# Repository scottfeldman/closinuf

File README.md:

# closinuf

**3D point scanner** — live 3D coordinates from four quadrature encoders on a Raspberry Pi, with a small web UI, foot‑switch capture, and FreeCAD‑friendly export.

## What it does

- Tracks **X**, **X'**, **Y**, **Z** from dedicated rotary encoders.  
- **Capture Point** in the browser or a **GPIO foot switch** appends the current **(X, Y, Z)** to a list (mm internally).
- **Save** downloads an **ASC** point cloud file, which can be imported into FreeCAD as a point cloud. 
- **Units** cycles mm → m → in → ft. **Zero** clears counts and points.
- **Short beep** on capture when audio output is available (speakers or HDMI).

## Hardware

See [HARDWARE.md](HARDWARE.md).

## Install on the Pi (`install.sh`)

1. On the Pi, clone the repository and enter the project directory:

   ```bash
   git clone https://github.com/scottfeldman/closinuf.git
   cd closinuf
   ```

2. Run the install script as root:

   ```bash
   sudo ./install.sh
   ```

3. Reboot if the installer prompts you to. 

What the script does:

- Enables **SPI** and relocates kernel CE pins off GPIO 8/7 (`dtoverlay=spi0-2cs,cs0_pin=12,cs1_pin=13`) in `/boot/firmware/config.txt`.
- Installs **`alsa-utils`** (`aplay` for capture beep) and **`golang-go`** if `go` is missing.
- Builds **`./closinuf`** in the repo.
- Adds the install user to **`spi`** and **`gpio`** groups (for local `go build` / debugging without the service).
- Installs **closinuf** **systemd** services: **`closinuf.service`** (app on :3000, runs as **root** for `/dev/mem` GPCLK, SPI, and GPIO), **`closinuf-browser.service`** (Chromium as install user)
- Prompts to **reboot** when SPI settings were added to `config.txt` (first install)

Useful commands:

```bash
sudo systemctl status closinuf closinuf-browser
sudo journalctl -u closinuf -f
```

## Manual run (development)

```bash
go build -o closinuf .
sudo ./closinuf
```

Open `http://127.0.0.1:3000`. Root is required for GPCLK setup (`/dev/mem`); the systemd service runs as root for the same reason.

## ASC export

One point per line: `X Y Z` in **millimeters** (space‑separated), suitable for FreeCAD point cloud import.

## Stack

Fiber, HTMX, gomponents, **LS7366R** counters over **SPI0**, **go-gpiocdev** (chip selects + foot switch).

## License

MIT — see [LICENSE](LICENSE).

## Author

Scott Feldman (2026)

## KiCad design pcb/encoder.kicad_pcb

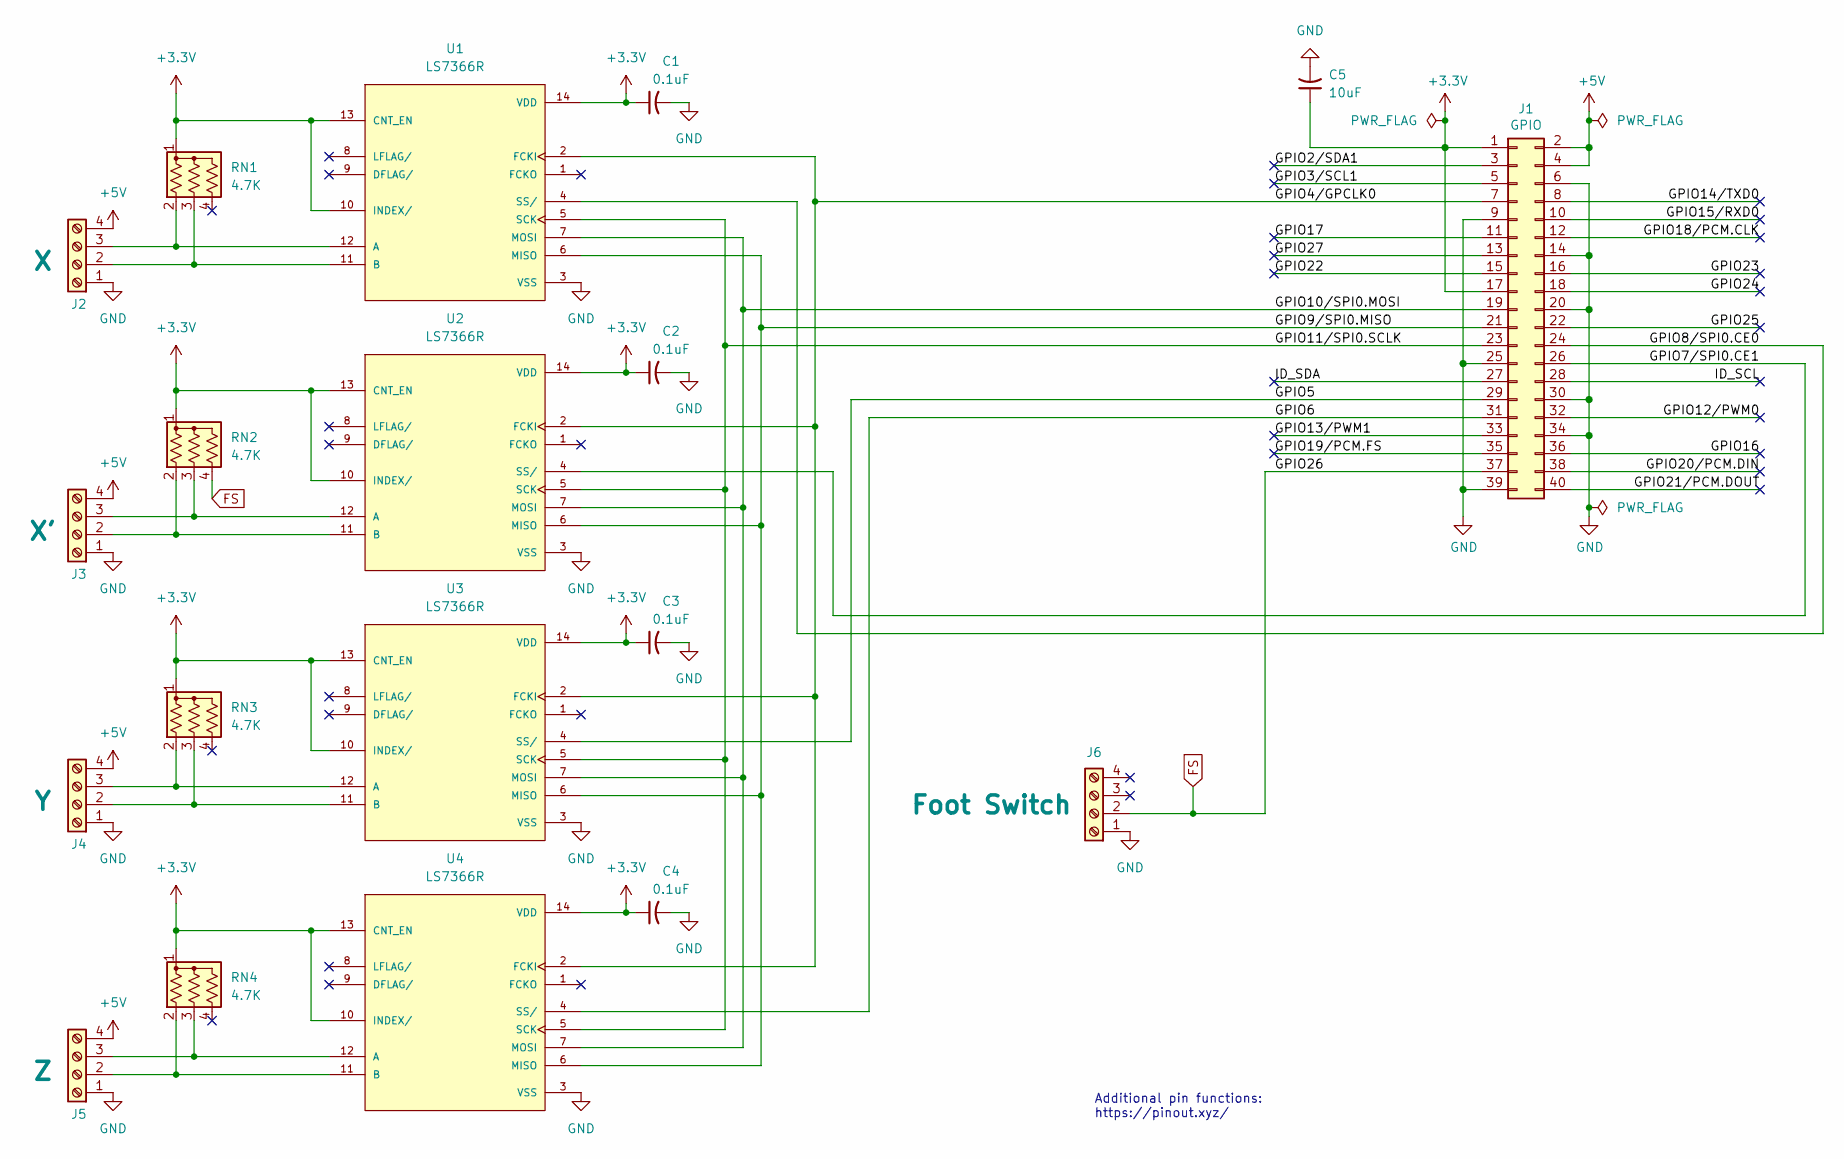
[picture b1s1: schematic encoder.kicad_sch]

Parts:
C1, C2, C3, C4: 0.1uF; C_Disc_D3.8mm_W2.6mm_P2.50mm; MPN FA18X8R1E104KNU00
C5: 10uF; C_Disc_D5.0mm_W2.5mm_P2.50mm; MPN FG14X7R1A106KRT00
J1: GPIO; PinSocket_2x20_P2.54mm_Vertical
J2: X; TerminalBlock_Phoenix_PT-1,5-4-5.0-H_1x04_P5.00mm_Horizontal
J3: X'; TerminalBlock_Phoenix_PT-1,5-4-5.0-H_1x04_P5.00mm_Horizontal
J4: Y; TerminalBlock_Phoenix_PT-1,5-4-5.0-H_1x04_P5.00mm_Horizontal
J5: Z; TerminalBlock_Phoenix_PT-1,5-4-5.0-H_1x04_P5.00mm_Horizontal
J6: Foot Switch; TerminalBlock_Phoenix_PT-1,5-4-5.0-H_1x04_P5.00mm_Horizontal
RN1, RN2, RN3, RN4: 4.7K; R_Array_SIP4; MPN 4604X-101-472LF
U1, U2, U3, U4: LS7366R; DIP762W45P254L1917H533Q14; PARTREV June 2014

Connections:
+3.3V: C1.1, C2.1, C3.1, C4.1, C5.1, J1.1, J1.17, RN1.1 (common), RN2.1 (common), RN3.1 (common), RN4.1 (common), U1.10 (INDEX/), U1.13 (CNT_EN), U1.14 (VDD), U2.10 (INDEX/), U2.13 (CNT_EN), U2.14 (VDD), U3.10 (INDEX/), U3.13 (CNT_EN), U3.14 (VDD), U4.10 (INDEX/), U4.13 (CNT_EN), U4.14 (VDD)
+5V: J1.2, J1.4, J2.4, J3.4, J4.4, J5.4
/GPIO2/SDA1: J1.3
/GPIO3/SCL1: J1.5
/GPIO4/GPCLK0: J1.7, U1.2 (FCKI), U2.2 (FCKI), U3.2 (FCKI), U4.2 (FCKI)
/GPIO5: J1.29, U3.4 (SS/)
/GPIO6: J1.31, U4.4 (SS/)
/GPIO7/SPI0.CE1: J1.26, U2.4 (SS/)
/GPIO8/SPI0.CE0: J1.24, U1.4 (SS/)
/GPIO9/SPI0.MISO: J1.21, U1.6 (MISO), U2.6 (MISO), U3.6 (MISO), U4.6 (MISO)
/GPIO10/SPI0.MOSI: J1.19, U1.7 (MOSI), U2.7 (MOSI), U3.7 (MOSI), U4.7 (MOSI)
/GPIO11/SPI0.SCLK: J1.23, U1.5 (SCK), U2.5 (SCK), U3.5 (SCK), U4.5 (SCK)
/GPIO12/PWM0: J1.32
/GPIO13/PWM1: J1.33
/GPIO14/TXD0: J1.8
/GPIO15/RXD0: J1.10
/GPIO16: J1.36
/GPIO17: J1.11
/GPIO18/PCM.CLK: J1.12
/GPIO19/PCM.FS: J1.35
/GPIO20/PCM.DIN: J1.38
/GPIO21/PCM.DOUT: J1.40
/GPIO22: J1.15
/GPIO23: J1.16
/GPIO24: J1.18
/GPIO25: J1.22
/GPIO27: J1.13
/ID_SCL: J1.28
/ID_SDA: J1.27
FS: J1.37, J6.2, RN2.4 (R3)
GND: C1.2, C2.2, C3.2, C4.2, C5.2, J1.6, J1.9, J1.14, J1.20, J1.25, J1.30, J1.34, J1.39, J2.1, J3.1, J4.1, J5.1, J6.1, U1.3 (VSS), U2.3 (VSS), U3.3 (VSS), U4.3 (VSS)
unnamed: J2.2, RN1.3 (R2), U1.11 (B)
unnamed: J2.3, RN1.2 (R1), U1.12 (A)
unnamed: J3.2, RN2.2 (R1), U2.11 (B)
unnamed: J3.3, RN2.3 (R2), U2.12 (A)
unnamed: J4.2, RN3.3 (R2), U3.11 (B)
unnamed: J4.3, RN3.2 (R1), U3.12 (A)
unnamed: J5.2, RN4.2 (R1), U4.11 (B)
unnamed: J5.3, RN4.3 (R2), U4.12 (A)

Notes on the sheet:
Additional pin functions: https://pinout.xyz/

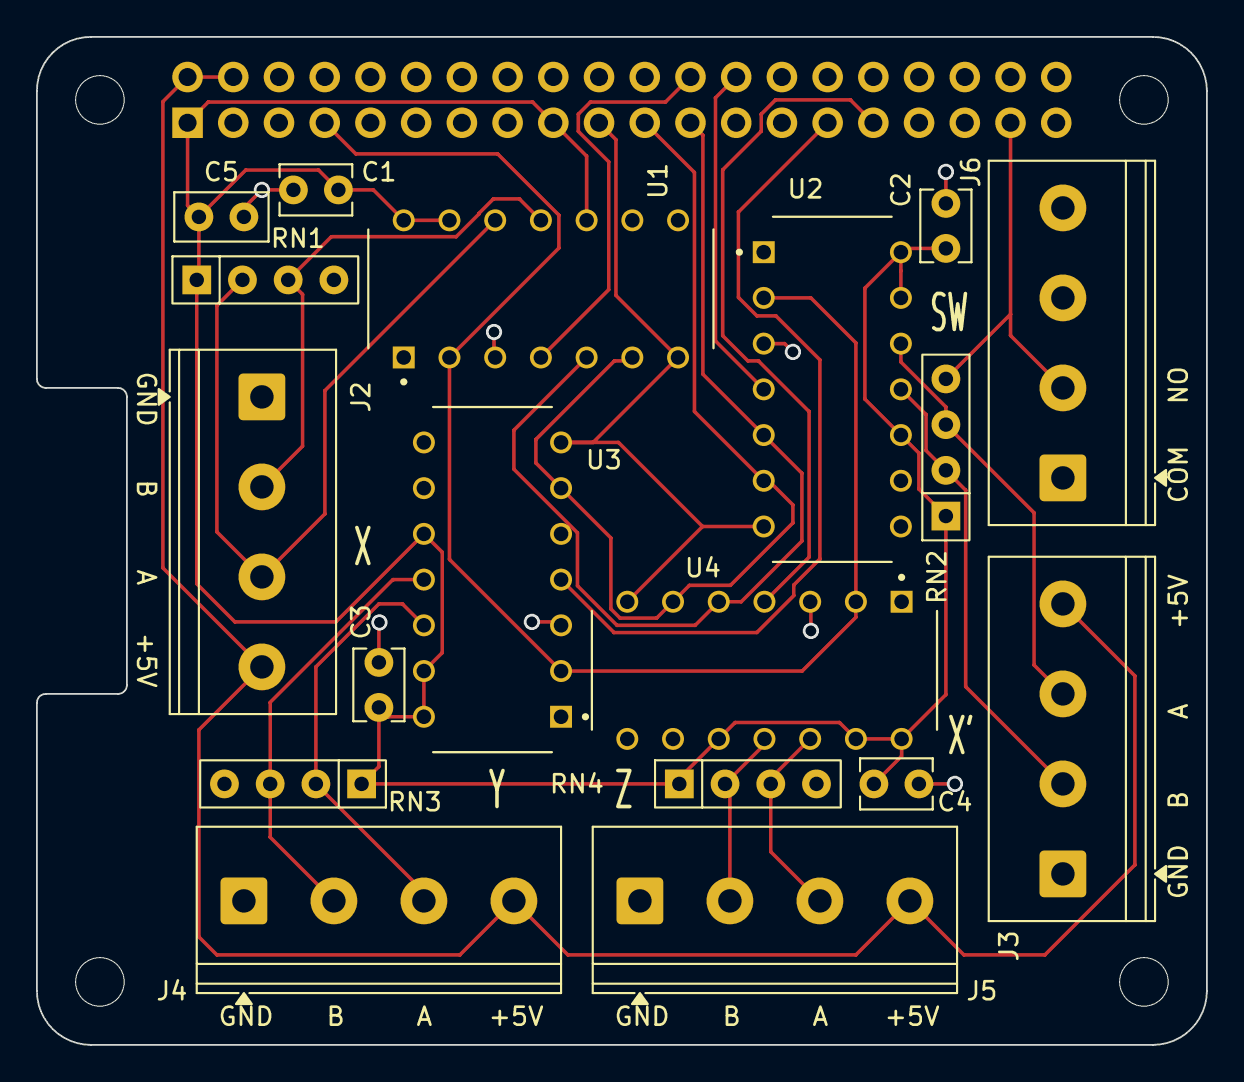
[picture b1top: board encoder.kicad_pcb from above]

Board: 2 copper layers, 65.0 x 56.0 mm, 23 parts (1 on the bottom side), 20 nets.

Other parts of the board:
MH1, MH2, MH3, MH4: MountingHole_2.7mm_M2.5

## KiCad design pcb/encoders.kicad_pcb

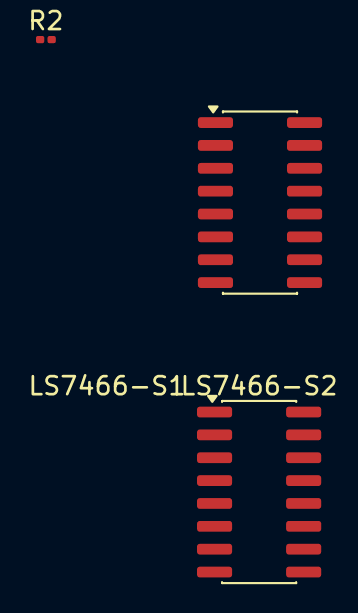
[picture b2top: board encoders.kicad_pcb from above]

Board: 2 copper layers, 7 parts (0 on the bottom side), 6 nets, no tracks yet.

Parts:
LS7466-S1, LS7466-S2: SOIC-16_3.9x9.9mm_P1.27mm
MH1, MH2, MH3, MH4: MountingHole_2.7mm_M2.5
R2: 4.7K; R_0201_0603Metric

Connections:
+3.3V: LS7466-S1.9 (CEx), LS7466-S1.14 (CEy), LS7466-S1.16 (VDD), LS7466-S2.9 (CEx), LS7466-S2.14 (CEy), LS7466-S2.16 (VDD), R2.1
GND: LS7466-S1.7 (Zx), LS7466-S1.8 (GND), LS7466-S1.13 (Zy), LS7466-S2.7 (Zx), LS7466-S2.8 (GND), LS7466-S2.13 (Zy)
unnamed: LS7466-S1.3 (MISO), LS7466-S2.3 (MISO)
unnamed: LS7466-S1.4 (MOSI), LS7466-S2.4 (MOSI)
unnamed: LS7466-S1.2 (SCK), LS7466-S2.2 (SCK)
unnamed: LS7466-S1.12 (By), R2.2

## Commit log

2026-01-16 first-check-in
2026-01-16 git ignore fp-info-cache
2026-01-16 site
2026-01-16 add encoder reader
2026-01-16 fixes
2026-01-16 cleanup
2026-01-17 save points
2026-01-18 add support for physical btn
2026-01-18 font stuff
2026-01-18 it's green
2026-01-22 working on puxh button
2026-01-22 fix wrong wiring on push button
2026-01-28 first checkin
2026-01-30 update 2x2 corners
2026-01-30 update PCB to add two more terminals
2026-01-30 add gerber file
2026-01-30 add README and update GPIO pins
2026-01-30 add url
2026-01-30 move site/ to top level
2026-02-06 final corner/uprights
2026-02-15 add X' and update GPIOs to match latest PCB
2026-03-19 update/add more CAD parts
2026-03-28 more parts
2026-04-01 more 3d parts
2026-04-01 revert to go 1.24.4
2026-04-01 add install.sh script
2026-04-02 fix import paths
2026-04-02 commecnt out some stuff for troubleshooting
2026-04-02 go mod tidy
2026-04-02 fix install script
2026-04-02 combine X and X' in UI and only show delta
2026-04-02 refresh README
2026-04-02 UI tweaks
2026-04-06 playing around with point cloud import
2026-04-06 fix some warnings
2026-04-27 add hardware.md to document hw
2026-04-27 updated schematic using ls7466s
2026-04-27 remove unnecessary files from pcb/
2026-04-27 update .gitignore to ignore all but the most importatnt pcb/ files
2026-04-27 add footprints
2026-04-27 redo schematic
2026-04-28 assign footprints
2026-04-28 snapshot...working on routing
2026-04-29 route with ls74633 chips
2026-04-29 update hardware.md to match schematic
2026-05-02 update BOM
2026-05-07 move to thru-hole resistors/caps to save costs
2026-05-07 sync hardware.md with BOM from schematic
2026-05-17 updated sw to use ls7366r hw counters
2026-05-18 gpclk scripts
2026-05-18 more cleanup
2026-05-18 add new files
2026-05-18 cleanup docs
2026-05-18 remove unused file
2026-05-18 add screen shot image
2026-05-18 update screen shot image
2026-05-18 add screen shot image to README
